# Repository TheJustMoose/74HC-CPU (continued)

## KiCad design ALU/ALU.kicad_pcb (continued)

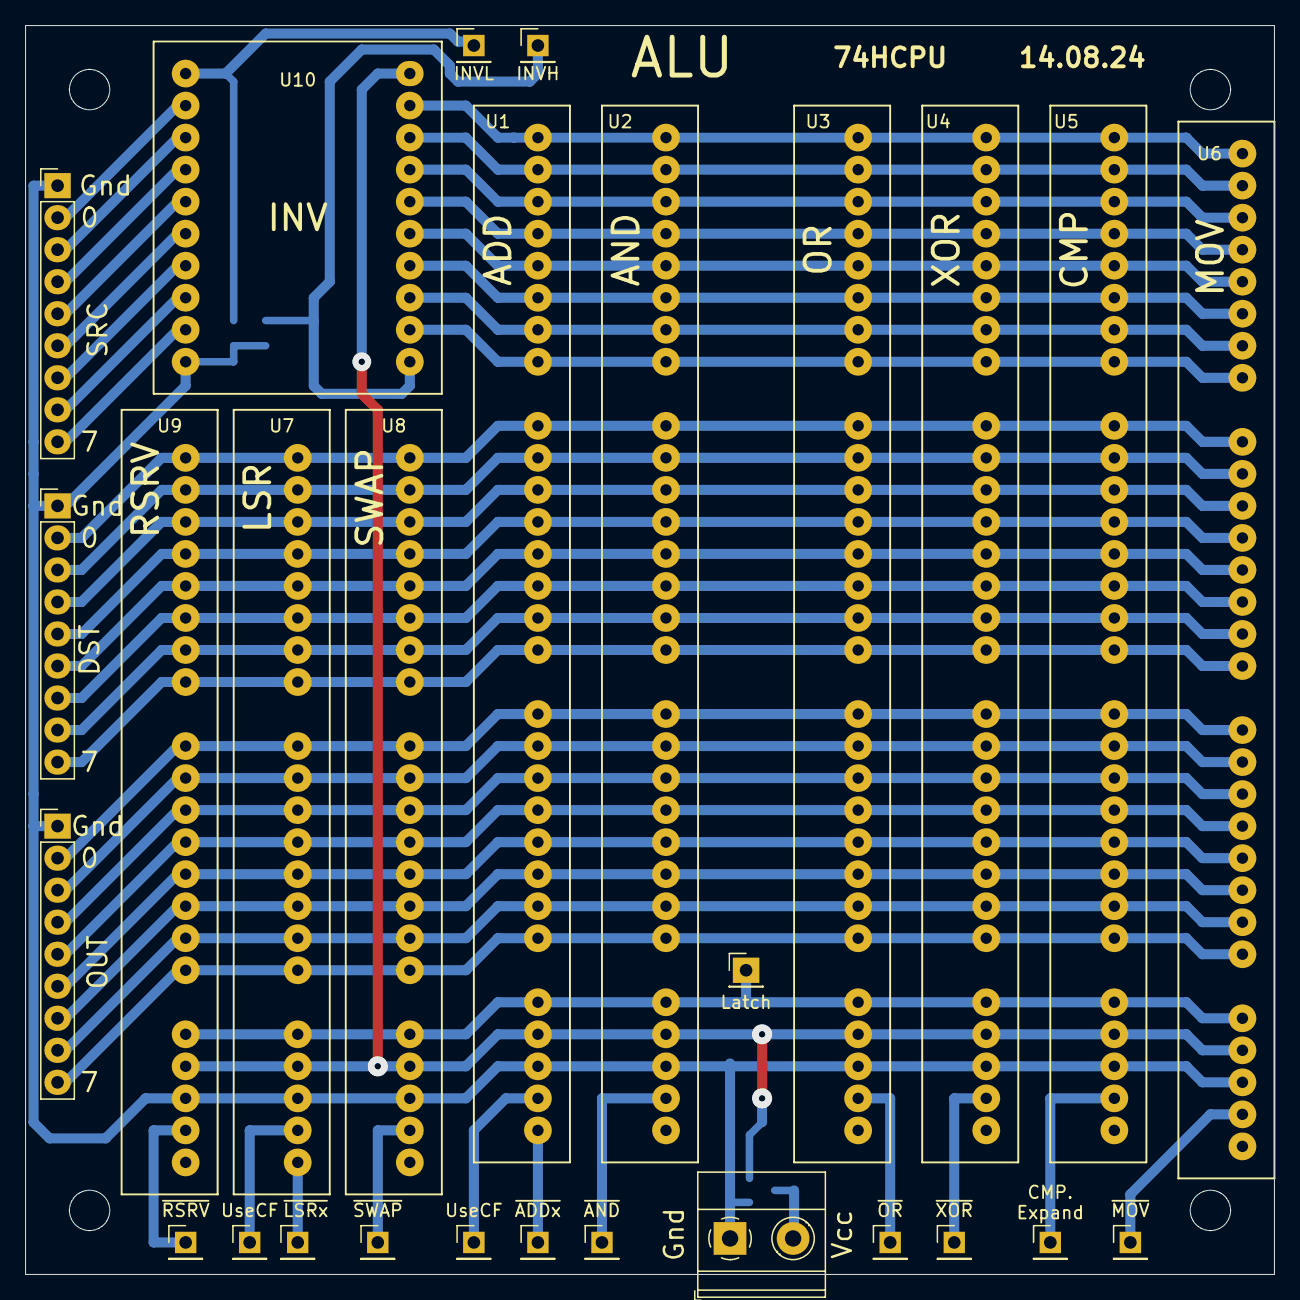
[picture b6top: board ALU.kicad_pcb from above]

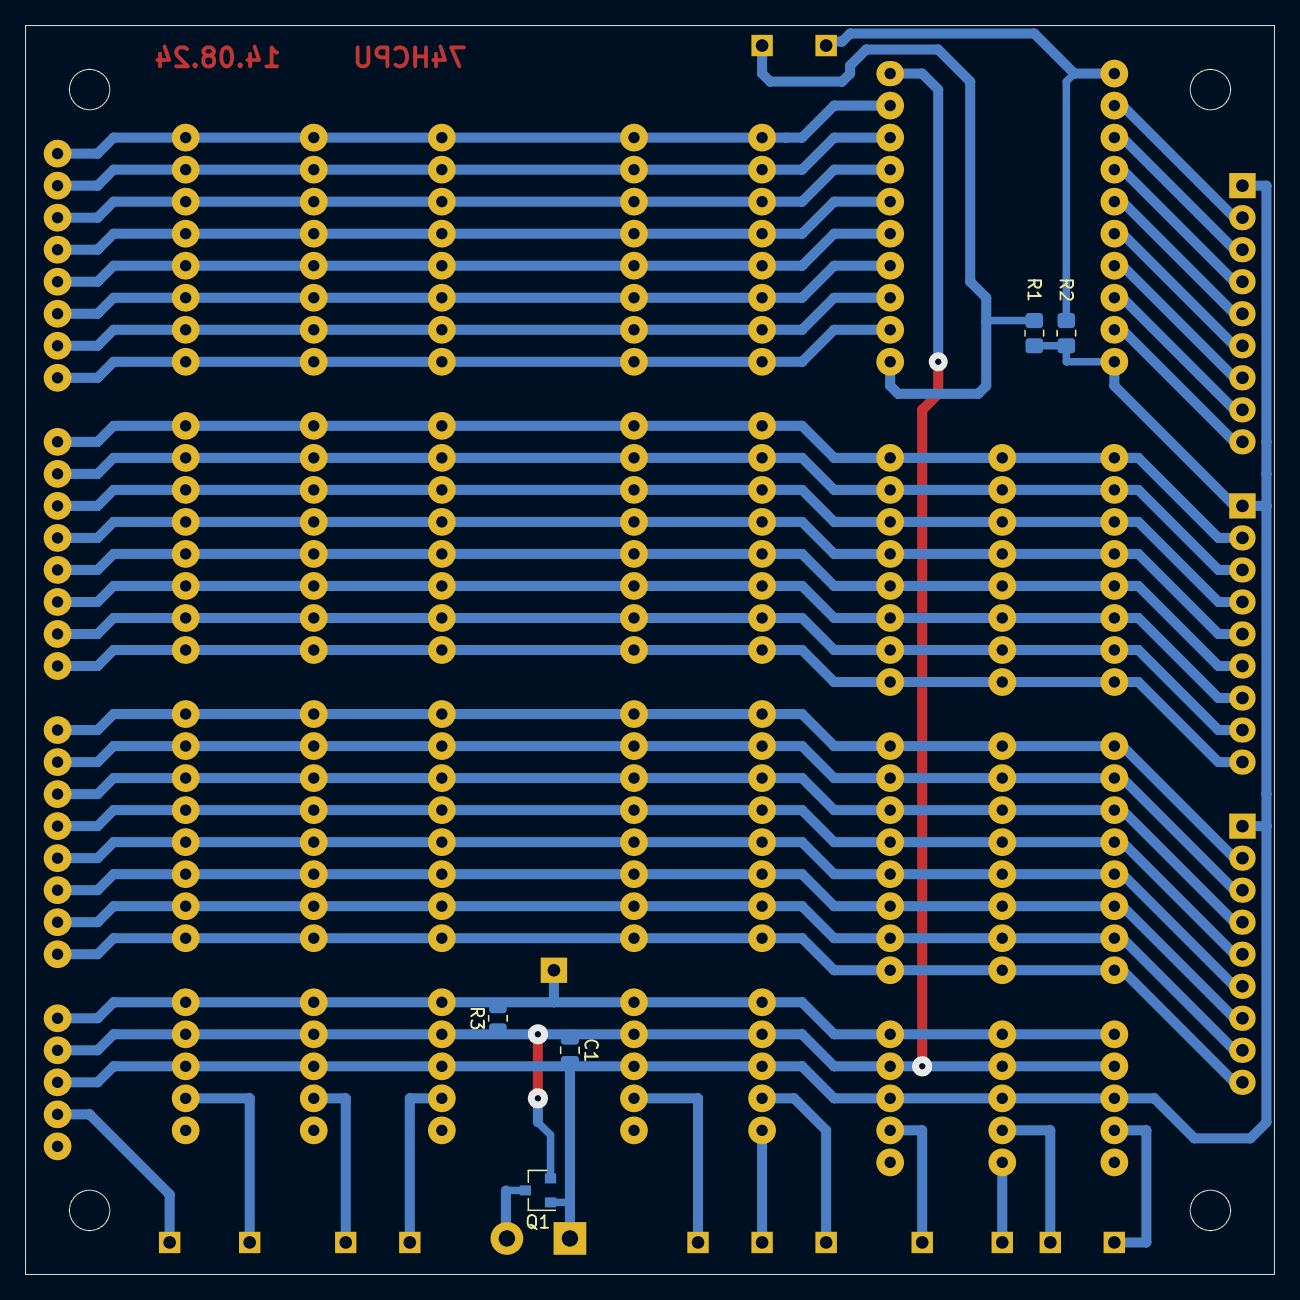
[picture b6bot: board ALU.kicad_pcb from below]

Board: 2 copper layers, 99.1 x 99.1 mm, 37 parts (5 on the bottom side), 49 nets.

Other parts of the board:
R1, R2, R3: 10k; R_0805_2012Metric_Pad1.20x1.40mm_HandSolder

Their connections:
/INVH: R1.1; also elsewhere on the board
/INVL: R2.1; also elsewhere on the board
/Latch: R3.2; also elsewhere on the board
GND: R1.2, R2.2; also elsewhere on the board
VCC: R3.1; also elsewhere on the board

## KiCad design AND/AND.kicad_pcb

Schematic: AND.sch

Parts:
C1: 0.1uF; C_Disc_D4.7mm_W2.5mm_P5.00mm
D1: LED; LED_0805_2012Metric_Pad1.15x1.40mm_HandSolder
J1, J2, J3: Conn_01x08_Male; PinHeader_1x08_P2.54mm_Horizontal
J4: Conn_01x04_Male; PinHeader_1x04_P2.54mm_Horizontal
R1: 1k; R_0805_2012Metric_Pad1.20x1.40mm_HandSolder
U1: 74LS573; DIP-20_W7.62mm
U2, U3: 74LS08; DIP-14_W7.62mm

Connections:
/A0: J1.8, U2.1
/A7: J1.1, U3.9
/B0: J2.8, U2.2
/B7: J2.1, U3.10
/Latch: J4.4, U1.11 (Load)
/O0: J3.8, U1.12 (Q7)
/O7: J3.1, U1.19 (Q0)
/~OE: J4.1, R1.1, U1.1 (OE)
GND: C1.2, D1.1, J4.2, U1.10 (GND), U2.7, U3.7
unnamed: D1.2, R1.2
unnamed: J1.2, U3.12
unnamed: J1.3, U3.4
unnamed: J1.4, U3.1
unnamed: J1.5, U2.9
unnamed: J1.6, U2.12
unnamed: J1.7, U2.4
unnamed: J2.2, U3.13
unnamed: J2.3, U3.5
unnamed: J2.4, U3.2
unnamed: J2.5, U2.10
unnamed: J2.6, U2.13
unnamed: J2.7, U2.5
unnamed: J3.2, U1.18 (Q1)
unnamed: J3.3, U1.17 (Q2)
unnamed: J3.4, U1.16 (Q3)
unnamed: J3.5, U1.15 (Q4)
unnamed: J3.6, U1.14 (Q5)
unnamed: J3.7, U1.13 (Q6)
unnamed: U1.2 (D0), U3.8
unnamed: U1.3 (D1), U3.11
unnamed: U1.4 (D2), U3.6
unnamed: U1.5 (D3), U3.3
unnamed: U1.6 (D4), U2.8
unnamed: U1.7 (D5), U2.11
unnamed: U1.8 (D6), U2.6
unnamed: U1.9 (D7), U2.3
VCC: C1.1, J4.3, U1.20 (VCC), U2.14, U3.14

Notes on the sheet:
Out
Ctrl

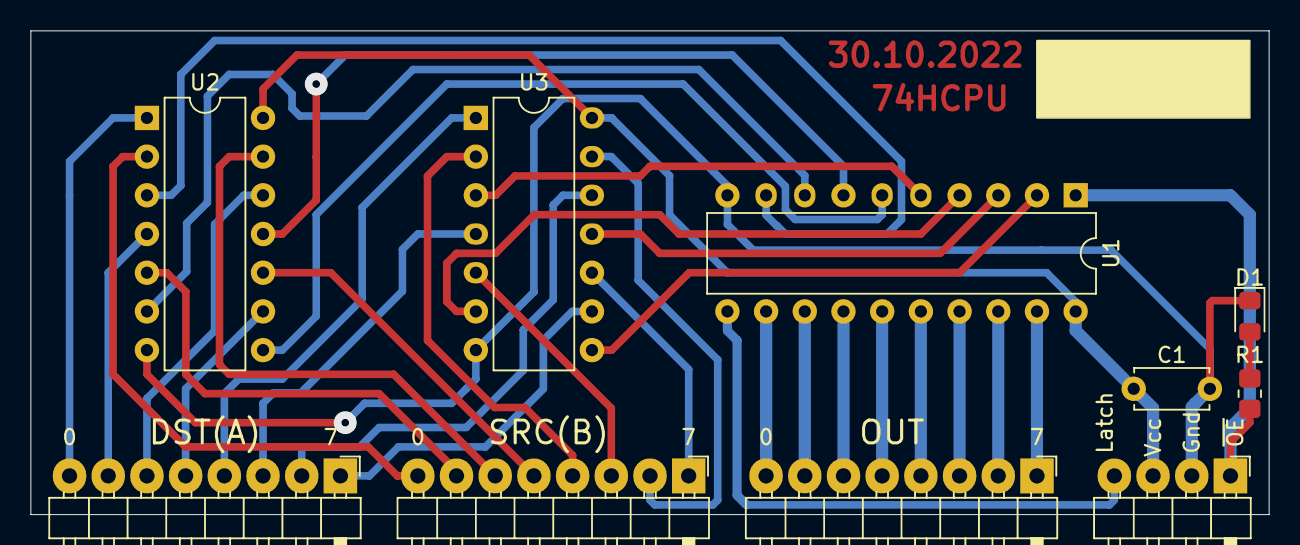
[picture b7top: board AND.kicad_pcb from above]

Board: 2 copper layers, 81.3 x 31.8 mm, 10 parts (0 on the bottom side), 37 nets.
